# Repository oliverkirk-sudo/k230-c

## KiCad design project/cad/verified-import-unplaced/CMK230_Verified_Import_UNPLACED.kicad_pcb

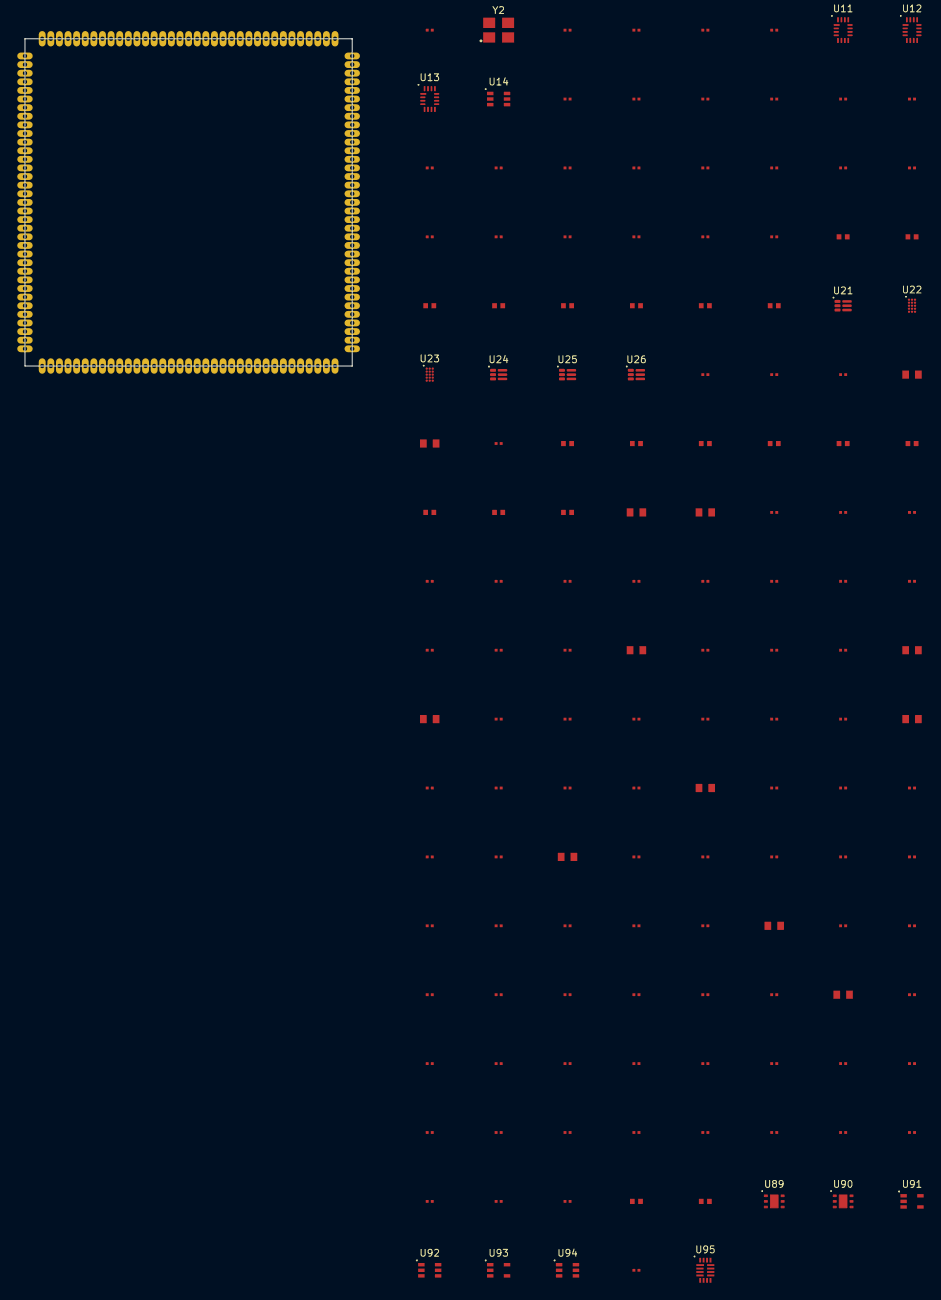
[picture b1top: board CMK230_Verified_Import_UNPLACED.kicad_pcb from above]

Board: 8 copper layers, 150 parts (0 on the bottom side), 49 nets, no tracks yet.

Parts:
C31, C32, C33, C34, C45, C61, C62, C63, C68, C205, C209, C215, C222, C227, C232, C233, C234, C235, C236, C237, C238, C239, C240, C241, C242, C243, C244, C245, C246, C503, C504, C505, C506, C507, C508, C509, C510, C511, C512, C513, C514, C515, C516, C518, C519, C520, C523, C524, C525, C526, C527, C528, C530, C531, C532, C533, C535, C536, C537, C538, C539, C542, C543, C544, C545, C546, C547, C548, C549, C550, C551, C554, C555, C556, C557, C558, C559, C560, C561, C564, C565, C566, C567, C568, C569, C570, C571, C572, C573, C574, C575, C576, C577, C809, C810, C811, C812, C813, C814, C816: 100nF CL03B104KP3NNWC CANDIDATE; Samsung_CL03B104KP3NNWC_MIDPOINT_LAND_DENSE_CANDIDATE
C66, C67, C501, C502, C517, C521, C522, C529, C534, C541, C553, C563: 4.7uF CL10B475KQ8NFQC CANDIDATE; Samsung_CL10B475KQ8NFQC_MIDPOINT_LAND_DENSE_CANDIDATE
J1: CM-K230 edge contract ONLY; CMK230_38x38_140P1_D0.50_Oval0.80x1.80_PROCESS_UNQUALIFIED
R63, R64, R65, R66: 240R TNPW0402 0.1pct 10ppm TOTAL<=0.70pct CANDIDA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; Vishay_TNPW0402_IPC7351_SourceLand_PROCESS_CANDIDATE
R67, R68: 30k TNPW0402 0.1pct 10ppm TOTAL<=0.70pct CANDIDATE; Vishay_TNPW0402_IPC7351_SourceLand_PROCESS_CANDIDATE
R69, R70, R71: 200R TNPW0402 0.1pct 10ppm TOTAL<=0.70pct CANDIDA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; Vishay_TNPW0402_IPC7351_SourceLand_PROCESS_CANDIDATE
R201: 3.32k TNPW0402 0.1pct 10ppm TOTAL<=0.70pct CANDID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; Vishay_TNPW0402_IPC7351_SourceLand_PROCESS_CANDIDATE
R202, R208, R211, R214, R526: 10k TNPW0402 0.1pct 10ppm TOTAL<=0.70pct CANDIDATE; Vishay_TNPW0402_IPC7351_SourceLand_PROCESS_CANDIDATE
R207: 8.66k TNPW0402 0.1pct 10ppm TOTAL<=0.70pct CANDID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; Vishay_TNPW0402_IPC7351_SourceLand_PROCESS_CANDIDATE
R210: 20k TNPW0402 0.1pct 10ppm TOTAL<=0.70pct CANDIDATE; Vishay_TNPW0402_IPC7351_SourceLand_PROCESS_CANDIDATE
R213: 45.3k TNPW0402 0.1pct 10ppm TOTAL<=0.70pct CANDID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; Vishay_TNPW0402_IPC7351_SourceLand_PROCESS_CANDIDATE
R525: 88.7k TNPW0402 0.1pct 10ppm TOTAL<=0.70pct CANDID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; Vishay_TNPW0402_IPC7351_SourceLand_PROCESS_CANDIDATE
U11, U12, U13: TMUX1574RSVR / CANDIDATE; TI_RSV0016A_TMUX1574_1.8x2.6_P0.4_DrawingVerified
U14: 74AUP1G97GW,125 SCHMITT OR CANDIDATE; Nexperia_SOT363-2_AUP1G97_DrawingVerified_CANDIDATE
U21: TPS62827ADMQ; TI_DMQ0006A_TPS6282xA_1.5x1.5_SMD_DrawingVerified
U22, U23: TPS628640BYCGR; TI_YCG0015_TPS628640_1.05x1.78_P0.35_SMD_DrawingVerified
U24, U26: TPS62826ADMQ; TI_DMQ0006A_TPS6282xA_1.5x1.5_SMD_DrawingVerified
U25: TPS62825ADMQ; TI_DMQ0006A_TPS6282xA_1.5x1.5_SMD_DrawingVerified
U89: TPS3808G01DRVR VIN GUARD; TI_DRV0006A_D_TPS3808_6P_EP7_DrawingVerified_CANDIDATE
U90: TPS3808G01DRVR RESET DELAY; TI_DRV0006A_D_TPS3808_6P_EP7_DrawingVerified_CANDIDATE
U91: 74AUP1G17GW,125 HIGH_TEMP CANDIDATE; Nexperia_SOT353-1_AUP1G17_06_DrawingVerified_CANDIDATE
U92, U94: 74AUP1G97GW,125 HIGH_TEMP CANDIDATE; Nexperia_SOT363-2_AUP1G97_DrawingVerified_CANDIDATE
U93: 74AUP1G06GW,125 HIGH_TEMP CANDIDATE; Nexperia_SOT353-1_AUP1G17_06_DrawingVerified_CANDIDATE
U95: NVT4858HKZ TF HS50 CANDIDATE; NXP_SOT1161-2_NVT4858HK_1.8x2.6_P0.4_DrawingVerified_CANDID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
Y2: X322524MOB4SI 24MHz CL12pF CANDIDATE; YXC_X322524MOB4SI_3225_4P_DrawingCandidate

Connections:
AVDD0P8_MIPI: C235.1, C246.1
AVDD1P8_MIPI: C240.1, C245.1
AVDD1P8_PMU: C238.1, C239.1
BANK0_VDDIO: C570.1, J1.107
BANK1_VDDIO: C571.1, J1.136
BANK2_VDDIO: C572.1, J1.90
BANK3_VDDIO: C573.1, J1.123
BANK4_VDDIO: C574.1, J1.23
BANK5_VDDIO: C575.1, J1.103
CODEC_VCM: C63.1, C66.1
CORE_PGOOD_5V: U21.2, U22.E1, U23.E1, U24.1, U25.1, U26.1
DDR_VREF: C61.2, C62.1, R65.2, R66.1
DISABLE_OR_TF: U13.13, U14.4
FB_1V8: R210.2, R211.1, U25.3
FB_3V3: R213.2, R214.1, U26.3
FB_CORE: R201.2, R202.1, U21.3
FB_DDR: R207.2, R208.1, U24.3
FIXED_RAILS_PGOOD_3V3: U24.2, U25.2, U26.2, U89.6, U92.3, U94.3
GLOBAL_DISABLE: U11.13, U12.13, U14.1, U93.4
GND: C31.2, C32.2, C33.2, C34.2, C45.2, C62.2, C63.2, C66.2, C67.2, C68.2, C205.2, C209.2, C215.2, C222.2, C227.2, C232.2, C233.2, C234.2, C235.2, C236.2, C237.2, C238.2, C239.2, C240.2, C241.2, C242.2, C243.2, C244.2, C245.2, C246.2, C501.2, C502.2, C503.2, C504.2, C505.2, C506.2, C507.2, C508.2, C509.2, C510.2, C511.2, C512.2, C513.2, C514.2, C515.2, C516.2, C517.2, C518.2, C519.2, C520.2, C521.2, C522.2, C523.2, C524.2, C525.2, C526.2, C527.2, C528.2, C529.2, C530.2, C531.2, C532.2, C533.2, C534.2, C535.2, C536.2, C537.2, C538.2, C539.2, C541.2, C542.2, C543.2, C544.2, C545.2, C546.2, C547.2, C548.2, C549.2, C550.2, C551.2, C553.2, C554.2, C555.2, C556.2, C557.2, C558.2, C559.2, C560.2, C561.2, C563.2, C564.2, C565.2, C566.2, C567.2, C568.2, C569.2, C570.2, C571.2, C572.2, C573.2, C574.2, C575.2, C576.2, C577.2, C809.2, C810.2, C811.2, C812.2, C813.2, C814.2, C816.2, J1.1, J1.2, J1.3, J1.36, J1.49, J1.57, J1.64, J1.71, J1.78, J1.89, J1.106, R64.2, R66.2, R69.2, R70.2, R71.2, R202.2, R208.2, R211.2, R214.2, R526.2, U11.6, U12.6, U12.8, U12.10, U12.11, U12.12, U13.1, U13.4, U13.6, U13.8, U13.11, U13.15, U14.2, U21.4, U22.A1, U22.B1, U22.B2, U22.B3, U23.A1, U23.B1, U23.B2, U23.B3, U24.4, U25.4, U26.4, U89.5, U89.7, U90.5, U90.7, U91.3, U92.1, U92.2, U93.3, U94.1, U94.2, U95.7, Y2.2, Y2.4
MIC_BIAS: C67.1, C68.1, J1.50
MODE_TF: U11.15, U12.15, U14.6
RESET_DELAYED_1V8: U90.6, U91.2
RESET_RELEASE_REQUEST_1V8: U90.4, U94.4
RSTN: C45.1, J1.122, U94.6
STORAGE_ENABLE_1V8: U92.4, U93.2
SW_CPU: U22.C1, U22.C2, U22.C3
SW_KPU: U23.C1, U23.C2, U23.C3
TFCARD_CLK: J1.21, U95.8
TFCARD_CMD: J1.22, U95.13
TFCARD_D0: J1.17, U95.10
TFCARD_D1: J1.18, U95.9
TFCARD_D2: J1.19, U95.12
TFCARD_D3: J1.20, U95.11
TF_HOST_CLK: U11.1, U95.5
TF_HOST_CMD: U11.4, U95.16
TF_HOST_D0: U11.8, U95.3
TF_HOST_D1: U11.11, U95.4
TF_HOST_D2: U12.1, U95.1
TF_HOST_D3: U12.4, U95.2
VDD0P8_CORE: C501.1, C502.1, C503.1, C504.1, C505.1, C506.1, C507.1, C508.1, C509.1, C510.1, C511.1, C512.1, C513.1, C514.1, C515.1, C516.1, R201.1
VDD0P8_CPU: C517.1, C518.1, C519.1, C520.1, U22.A3
VDD0P8_DDR_CORE: C233.1, C529.1, C530.1, C531.1, C532.1, C533.1
VDD0P8_KPU: C521.1, C522.1, C523.1, C524.1, C525.1, C526.1, C527.1, C528.1, U23.A3
VDD1P1_DDR_IO: C61.1, C534.1, C535.1, C536.1, C537.1, C538.1, C539.1, C541.1, C542.1, C543.1, C544.1, C545.1, C546.1, C547.1, C548.1, C549.1, C550.1, C551.1, C553.1, C554.1, C555.1, C556.1, C557.1, C558.1, C559.1, C560.1, C561.1, R63.2, R65.1, R207.1
VDD1P8: C563.1, C564.1, C565.1, C566.1, C567.1, C568.1, C569.1, C576.1, C577.1, C809.1, C810.1, C811.1, C812.1, C813.1, C814.1, J1.8, R210.1, U89.1, U89.4, U90.1, U90.2, U91.5, U92.5, U93.5, U94.5, U95.15
VDD_3V3: C31.1, C32.1, C33.1, C34.1, C816.1, J1.7, R213.1, U11.14, U12.14, U13.14, U14.3, U14.5, U95.14
VIN_5V: C205.1, C209.1, C215.1, C222.1, C227.1, C232.1, J1.4, J1.5, J1.6, R67.1, R68.1, R525.1, U21.6, U22.D1, U22.D2, U22.D3, U23.D1, U23.D2, U23.D3, U24.6, U25.6, U26.6
VIN_GUARD_SENSE: R525.2, R526.1, U89.2

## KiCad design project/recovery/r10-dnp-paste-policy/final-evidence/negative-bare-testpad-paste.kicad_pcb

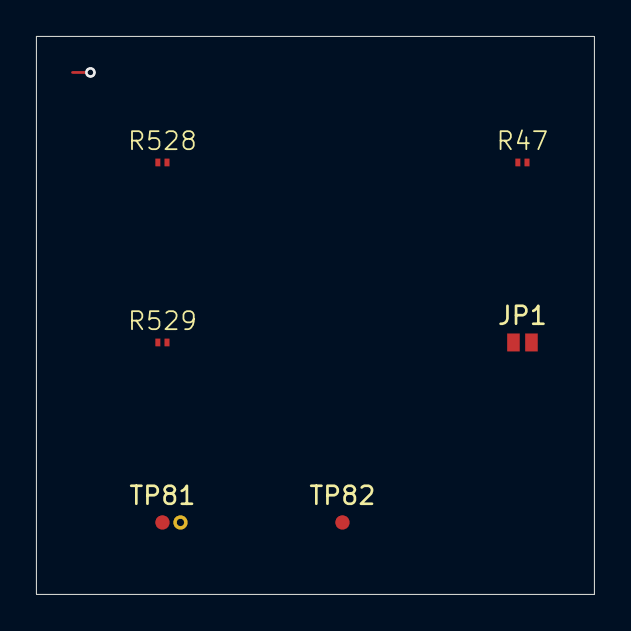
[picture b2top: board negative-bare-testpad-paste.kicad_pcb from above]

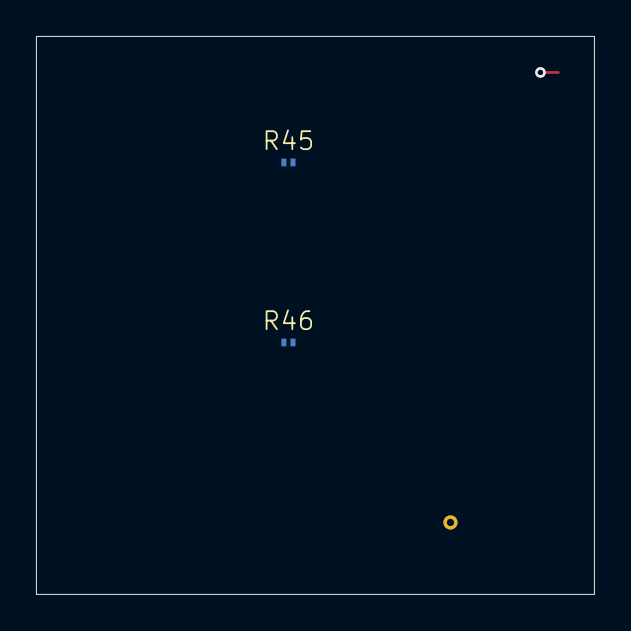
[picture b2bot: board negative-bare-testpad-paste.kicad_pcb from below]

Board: 2 copper layers, 31.0 x 31.0 mm, 8 parts (2 on the bottom side), 4 nets.

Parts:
JP1: OPEN=EMMC / CLOSED=TF; COLD ONLY; Core_Cold_Selector_Open_SolderBridge_CANDIDATE
R45: 10k BOOT0 HIGH / DNP; Vishay_CRCW0201_SourceLand_PROCESS_CANDIDATE
R46: 10k BOOT1 HIGH; Vishay_CRCW0201_SourceLand_PROCESS_CANDIDATE
R47: 10k BOOT1 LOW / DNP; Vishay_CRCW0201_SourceLand_PROCESS_CANDIDATE
R528: 0R QUALIFICATION STRAP DNP; Vishay_CRCW0201_SourceLand_PROCESS_CANDIDATE
R529: 100k DEFAULT INHIBIT; Vishay_CRCW0201_SourceLand_PROCESS_CANDIDATE
TP81: PMU OUT0 OBSERVE ONLY; Core_PMUSTATUS_Top_TestPad_0p8_CANDIDATE
TP82: PMU OUT1 OBSERVE ONLY; Core_PMUSTATUS_Top_TestPad_0p8_CANDIDATE

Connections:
BOOT1: R46.1, R47.1
BOOT_VOLTAGE_QUALIFIED_1V8: R528.2, R529.1
GND: R47.2, R529.2
VDD1P8: R45.2, R46.2, R528.1
